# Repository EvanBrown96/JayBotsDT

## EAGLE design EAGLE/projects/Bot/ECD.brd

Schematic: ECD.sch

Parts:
C1: 330n; C025-025X050
C2: 100n; C025-025X050
IC2: 7805T; TO220H
JP2: PINHD-1X2; 1X02
JP7: SHIELD_PWR; 1X02_XTRA_BIG
KK1: SK129-PAD; SK129
LED1, LED2, LED3: LED5MM
PI: RASPI_BOARD_B+_F; RASPI_BOARD_B+_FULL
R1, R2: 1k; 0207/10
R3, R4: 2k; 0207/10
R5: 10; 0207/10
R6: 100; 0207/10
S2: MS243
U3: ARDUINO_SHIELDLABEL; DUEMILANOVE_SHIELD
U$1, U$2: ULTRASONIC-HC-SR04

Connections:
0: C1.2, C2.2, IC2.2 (GND), JP2.1, PI.6 (GND), R3.2, R4.2, R5.1, R6.1, S2.2 (S), U3.GND@0 (GND), U3.GND@1 (GND), U3.GND@2 (GND), U$1.4 (GND), U$2.4 (GND); also elsewhere on the board
L_BCK: PI.40 (GPIO21); also elsewhere on the board
L_FWD: PI.38 (GPIO20); also elsewhere on the board
L_SPD: PI.32 (GPIO12), U3.D5 (*D5)
L_US_ECHO: PI.18 (GPIO24), R1.1, R3.1
L_US_TRIG: PI.16 (GPIO23), U$1.2 (TRIG)
unnamed: R1.2, U$1.3 (ECHO)
unnamed: R2.2, U$2.3 (ECHO)
unnamed: LED3.A, PI.22 (GPIO25)
unnamed: LED1.K (C), LED2.K (C), R5.2
unnamed: LED3.K (C), R6.2
unnamed: JP7.2, S2.1
unnamed 12: U3.D4; also elsewhere on the board
unnamed 13: U3.D7; also elsewhere on the board
unnamed 14: U3.D8; also elsewhere on the board
unnamed 15: U3.D9 (*D9); also elsewhere on the board
PI_3V3: PI.1 (3V3); also elsewhere on the board
PI_5V: C2.1, IC2.3 (VO), LED1.A, LED2.A, PI.2 (5V0), U3.5V, U3.A0, U3.A1, U$1.1 (VCC), U$2.1 (VCC); also elsewhere on the board
PWR+: C1.1, IC2.1 (VI), JP2.2, JP7.1
R_BCK: PI.31 (GPIO06); also elsewhere on the board
R_FWD: PI.29 (GPIO05); also elsewhere on the board
R_SPD: PI.33 (GPIO13), U3.D6 (*D6)
R_US_ECHO: PI.15 (GPIO22), R2.1, R4.1
R_US_TRIG: PI.13 (GPIO27), U$2.2 (TRIG)

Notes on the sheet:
PWR +
PWR -

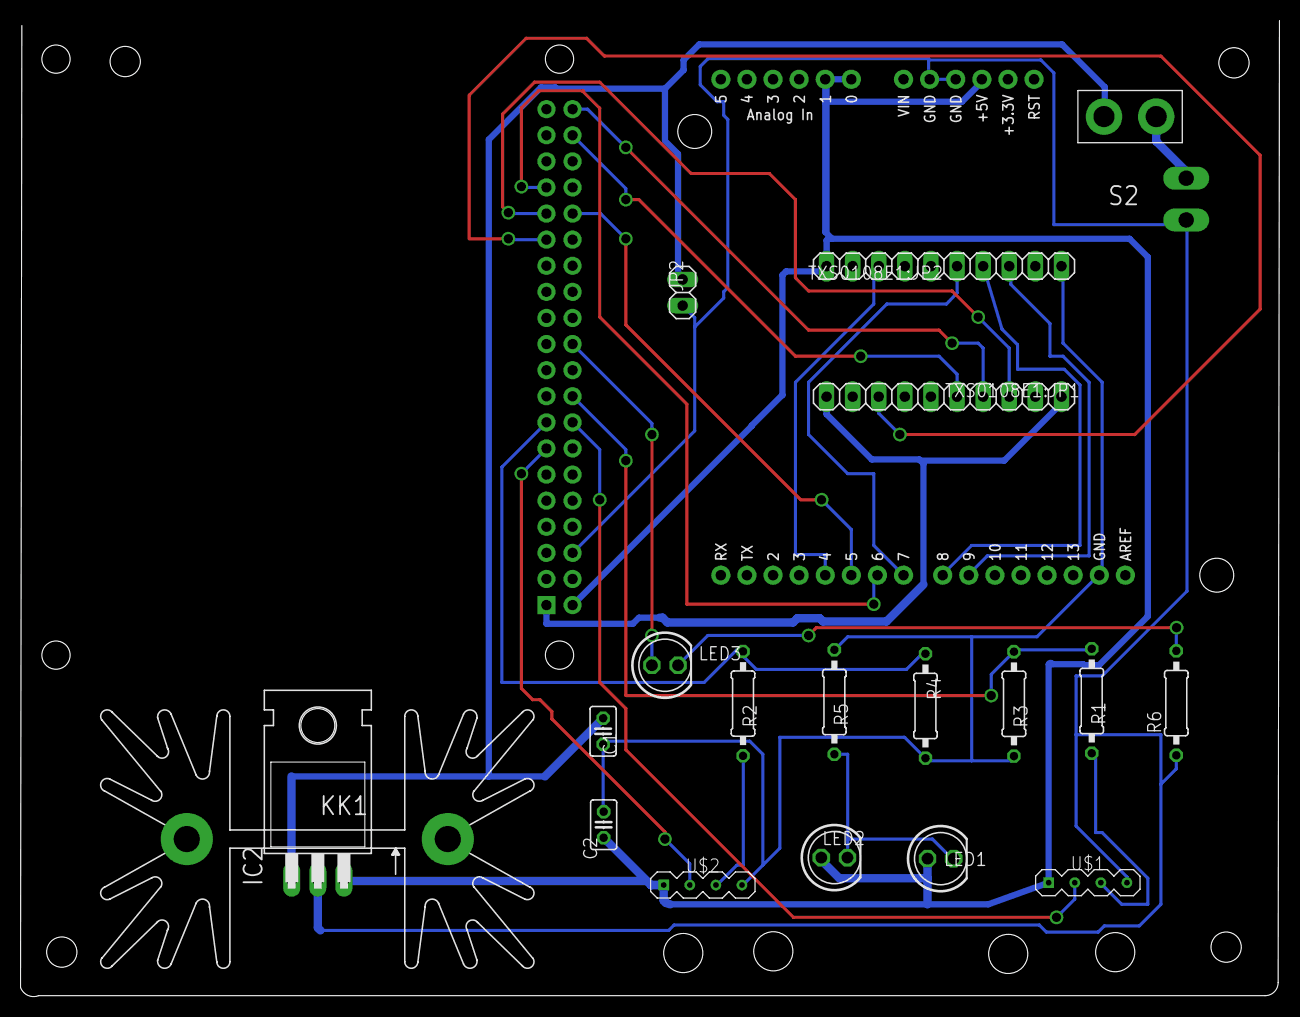
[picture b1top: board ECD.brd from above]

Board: 2 copper layers, 122.5 x 95.0 mm, 22 parts (1 on the bottom side), 24 nets.

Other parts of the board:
TXS0108E1:JP1, TXS0108E1:JP2: 1X10

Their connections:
0: TXS0108E1:JP2.1; also elsewhere on the board
L_BCK: TXS0108E1:JP1.7; also elsewhere on the board
L_FWD: TXS0108E1:JP1.6; also elsewhere on the board
unnamed 12: TXS0108E1:JP2.8; also elsewhere on the board
unnamed 13: TXS0108E1:JP2.5; also elsewhere on the board
unnamed 14: TXS0108E1:JP2.4; also elsewhere on the board
unnamed 15: TXS0108E1:JP2.3; also elsewhere on the board
PI_3V3: TXS0108E1:JP1.1, TXS0108E1:JP1.10; also elsewhere on the board
PI_5V: TXS0108E1:JP2.10; also elsewhere on the board
R_BCK: TXS0108E1:JP1.8; also elsewhere on the board
R_FWD: TXS0108E1:JP1.3; also elsewhere on the board

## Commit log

2020-02-03 add initial comms prototyping files
2020-02-03 finished early prototype
2020-02-18 reversed server and client
2020-02-18 renamed folders
2020-02-24 added pwm setting
2020-02-25 finished logic for rover speed and direction choice
2020-02-25 fixed number conversion
2020-02-25 fixed pwm levels
2020-02-27 add basic sensing code
2020-03-06 add rovercontroller winforms starting project
2020-03-07 add remote control exe
2020-03-09 start of rover info displays
2020-03-10 finish adding connections, background worker for testing connectivity
2020-03-10 improve thread safety
2020-03-10 add start of tab layout, improve layout of program
2020-03-10 add message queueing, some documentation
2020-03-11 finished user-facing part of manual controller
2020-03-11 add code to create tab upon new connection
2020-03-12 finish adding manual control to application
2020-03-12 improve drawing of manual controller; partially implemented disconnect button
2020-03-12 updated embedded code to work with winforms app
2020-03-14 finish implementing disconnect functionality
2020-03-14 forgot to multiply by half
2020-03-16 fixed dumb error causing motors not to stop immediately
2020-03-16 add big try catch:
2020-03-16 add second sensor code
2020-03-16 fix string error
2020-03-16 add 100*
2020-03-16 add extra exception thing
2020-03-16 add sys kill
2020-03-16 Add files via upload
    file needed to create node that will drive the motors through ros
2020-03-16 update gitignore
2020-03-16 update ignore files
2020-03-16 remove binary files initially
2020-03-16 add back executable
2020-03-20 add eagle schematic files
2020-03-20 replaced TXS0108E with module
2020-03-28 changes for distance display
2020-03-28 Speed up left motor driver to adjust rover left vear.
2020-03-29 progress with improving sockets
2020-03-29 added indicator to new code
2020-03-29 add handling for killing threads/sockets
2020-03-29 update exe
2020-03-29 fixed dumb error
2020-03-29 create catkin workspace
2020-03-30 add jaybot package
2020-03-30 revert changes for distance sensing
2020-03-30 actually reverted changes
2020-03-30 fixed movement script
2020-03-30 re-added EAGLE files that were accidentally removed
2020-03-30 Add files via upload
    these programs take in the data from the ultrasonic sensors and put them in arrays in cm.
2020-03-31 Add files via upload
    test file for autonomous driving
2020-04-04 Add files via upload
    test for rover movement with keyboard
2020-04-04 Designed US mounting
    yep
2020-04-04 added initial versions of avoidance, movement logic, user interface, and motor driver nodes
2020-04-04 fixed line endings:
2020-04-04 fixed execute permissions
2020-04-04 fixed publisher and socket problems
2020-04-04 fixed user interface errors
2020-04-04 added namespaces to topics
2020-04-04 fixed type
2020-04-04 add test video
2020-04-04 add picutre
2020-04-04 test pic
2020-04-04 add pic
2020-04-04 Add livstream file
2020-04-04 remove test pictures
2020-04-05 fixed issue with commands becoming offset; fixed speed unevenness, somewhat
2020-04-05 wrong word
2020-04-05 undo
2020-04-05 wrong number
2020-04-05 error correct
2020-04-05 Create autonomousTest.py
    trying to open in remote folder
2020-04-05 moving
    move
2020-04-05 revert eagle files
2020-04-06 add setup file
2020-04-06 improve setup file
2020-04-06 improve setup file more
2020-04-06 slight update to ros package
2020-04-06 rebuild package
2020-04-06 Not finished routing
    Not finished routing
2020-04-06 improved avoidance sensor code
2020-04-06 missing parenthesis
2020-04-06 missing import
2020-04-07 update movement logic node to stop if it senses an obstacle during manual control
2020-04-07 update user interface node for better stability
2020-04-07 fixed errors
2020-04-07 fixed rover stopping when coming close to wall no matter the direction
2020-04-07 error with global variables
2020-04-07 fixed globals
2020-04-07 add debug printouts
2020-04-07 final globals update, i hope
2020-04-07 add launch file
2020-04-07 update logging
2020-04-07 add autonomous code
2020-04-07 simplified socket code
2020-04-08 Final PCB
    PCB
2020-04-08 Almost error free
    .
2020-04-08 Delete EAGLE.tar.gz
    del
2020-04-08 Ready to mill
2020-04-09 improved setup script
2020-04-09 RedoPCB
2020-04-10 add blinker LED
2020-04-10 fixed switch position
2020-04-10 Shoot me!
2020-04-11 update setup file
2020-04-11 fix firmware update command
2020-04-12 add initial remote repo
2020-04-12 finish gui wrapper node, improved launch file
2020-04-13 update setup files, add rplidar submodule
2020-04-13 improve setup files further
2020-04-13 update project to use rosbridge
2020-04-13 update standard.launch to remove user interface node
2020-04-13 add run.bat file to start gui and rosbridge
2020-04-13 improve run.bat
2020-04-13 improve setup files
2020-04-13 improve run.bat, add rplidarNode to launch file
2020-04-13 add hector slam launch file
2020-04-13 remove devel folder
2020-04-13 update launch file
2020-04-13 remove redudancy'
2020-04-14 restructured files
2020-04-14 improved set & env files
2020-04-14 add laucher node
2020-04-15 add ros-sharp module
2020-04-15 improve launcher node & launch file
2020-04-15 work on gui app
2020-04-15 add catkin_make calls to setup files
2020-04-15 make launcher executeable
2020-04-15 update rpi launcher
2020-04-15 add more message types & handlgers
2020-04-15 finish up launcher node
2020-04-15 update service file
2020-04-15 updated controller for thread safety, polling, and killing launched nodes
2020-04-15 remove old code
2020-04-16 add working environment setup for remote launch
2020-04-16 add logging to nodes
2020-04-16 update environment files, launcher
2020-04-16 fix env set
2020-04-16 add blinker
2020-04-16 add docker files
2020-04-16 fix dockerfile
2020-04-17 further work on dockerfile setup
2020-04-17 fixed line endings
2020-04-17 Add files via upload
    added lidar avoidance into the movement logic file
2020-04-17 increase distance for US
2020-04-17 PCB Updates
2020-04-17 fix ip get
2020-04-17 fixed launcher
2020-04-17 add install call for pycrypto
2020-04-17 more dockerfile updates
2020-04-17 add env setup file with IP set
2020-04-17 stupid
2020-04-17 fixed wrong setup env file
2020-04-17 printout error messages if launcher instance is killed
2020-04-17 Finished updating GUI app and run.bat for new changes
2020-04-17 fixed launch arg
2020-04-17 setup stuff
2020-04-17 launchfile testing
2020-04-17 add rplidar_ros install to dockerfile
2020-04-17 add debug .bat, add hector_slam node to launchfile
2020-04-17 attempt to run hectorslam on main node instead
2020-04-17 minor shifting around of setup stuff
2020-04-17 add boot script to allow access to LiDAR
2020-04-17 cleanup
2020-04-18 update release exe files
2020-04-18 make it so rviz starts along with application
2020-04-18 one additional echo
2020-04-19 update debug file
2020-04-19 replace cat with type for windows
2020-04-19 fix avoidance node
2020-04-19 replace rm with windows del
2020-04-19 replace sleep with windows timeout
2020-04-20 add updated hector_slam checkout
2020-04-21 updates to display camera output
2020-04-21 add raspicam dependency
2020-04-21 update launch files
2020-04-21 update nodes to create in correct namespace
2020-04-22 improve launch files
2020-04-23 updates to namespacing, etc
2020-04-23 add blinker node
2020-04-23 fix blinker node
2020-04-23 add blinker to launch file
2020-04-24 fix pin polarities
2020-04-24 again fix
2020-04-24 decrease speed
2020-04-24 add reset map and show map buttons and according functionality
2020-04-25 increase blink time
2020-04-25 test inverted lidar
2020-04-25 rebuild exe
2020-04-26 simplification of embedded code into threads instead of nodes
2020-04-26 update package files
2020-04-26 fixes to movement logic
2020-04-26 fixed permissions on driver_node
2020-04-26 move printout
2020-04-27 stopped rviz opening terminal window
2020-04-27 fixes
2020-04-27 fix fwd movement stopping
2020-04-27 update remote to reflect changes on rover
2020-04-27 add lidar avoidance
2020-04-27 add autonomous logic with lidar
2020-04-28 improve atonomous logic
2020-04-28 fix logic
2020-04-28 syntax
2020-04-29 update mapping algorithm
2020-04-29 fix manual control
2020-04-29 more fixes
2020-04-29 even more fixes
2020-04-29 locks
2020-04-29 fixed infinite loop
2020-04-29 fix too_far
2020-04-29 better slam params
2020-04-29 update slam config
2020-04-29 rebuilt exe
2020-04-29 make avoidance operable either with threads or ros nodes
2020-04-29 make driver node operable either with threads or ros nodes
2020-04-29 clarity in movement_logic
2020-04-29 remove blinker
2020-04-30 rover speed now controllable in manual mode
2020-04-30 remove extra files
2020-04-30 add multirobot-map-explore package & test launchfile
2020-04-30 minor fixes
2020-04-30 add support for toggling obstacle avoidance in manual mode
2020-05-01 fix build issues
2020-05-01 conversion problem
2020-05-03 fix method name
2020-05-03 improve mapping algorithm slightly
2020-05-03 added images
2020-05-03 initial pathfinding code
2020-05-06 (almost) finish path-building alg
2020-05-06 finish initial implementation of pathfinding
2020-05-07 add pathfinding code to gui
2020-05-07 fixed mistakes, added logging
2020-05-07 build gui
2020-05-07 add missing lines
2020-05-07 copy changes from pathfinding branch
2020-05-07 updates tologging, logic
2020-05-07 Fixed voltage reg on Eagle
2020-05-08 add termination condition
2020-05-08 rebuild exe, remove speed resets
2020-05-10 uncomment wall code in path_create, add to launch file
2020-05-10 update rviz files
2020-05-10 fix atan giving reversed directions
2020-05-10 fix path following
2020-05-10 add path reduction
2020-05-10 improve path follow
2020-05-11 restructure path following
2020-05-11 more restructuring
2020-05-11 fix errors
2020-05-11 fix vel estimates going to 0
2020-05-11 fix wall expansion
2020-05-11 fixed missing global
2020-05-16 remove unused code
2020-05-17 add bot_display update
2020-05-17 Updated Eagle Wired diagram
2022-06-22 Bump Newtonsoft.Json in /RoverController/RoverController
    Bumps [Newtonsoft.Json](https://github.com/JamesNK/Newtonsoft.Json) from 12.0.3 to 13.0.1.
    - [Release notes](https://github.com/JamesNK/Newtonsoft.Json/releases)
    - [Commits](https://github.com/JamesNK/Newtonsoft.Json/compare/12.0.3...13.0.1)
    ---
    updated-dependencies:
    - dependency-name: Newtonsoft.Json
2022-12-08 Bump Newtonsoft.Json in /RoverController/RoverController
    Bumps [Newtonsoft.Json](https://github.com/JamesNK/Newtonsoft.Json) from 12.0.3 to 13.0.2.
    - [Release notes](https://github.com/JamesNK/Newtonsoft.Json/releases)
    - [Commits](https://github.com/JamesNK/Newtonsoft.Json/compare/12.0.3...13.0.2)
    ---
    updated-dependencies:
    - dependency-name: Newtonsoft.Json

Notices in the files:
parts and their libraries:
diy-modules: Released under the Creative Commons Attribution 4.0 International License: http://creativecommons.org/licenses/by/4.0
